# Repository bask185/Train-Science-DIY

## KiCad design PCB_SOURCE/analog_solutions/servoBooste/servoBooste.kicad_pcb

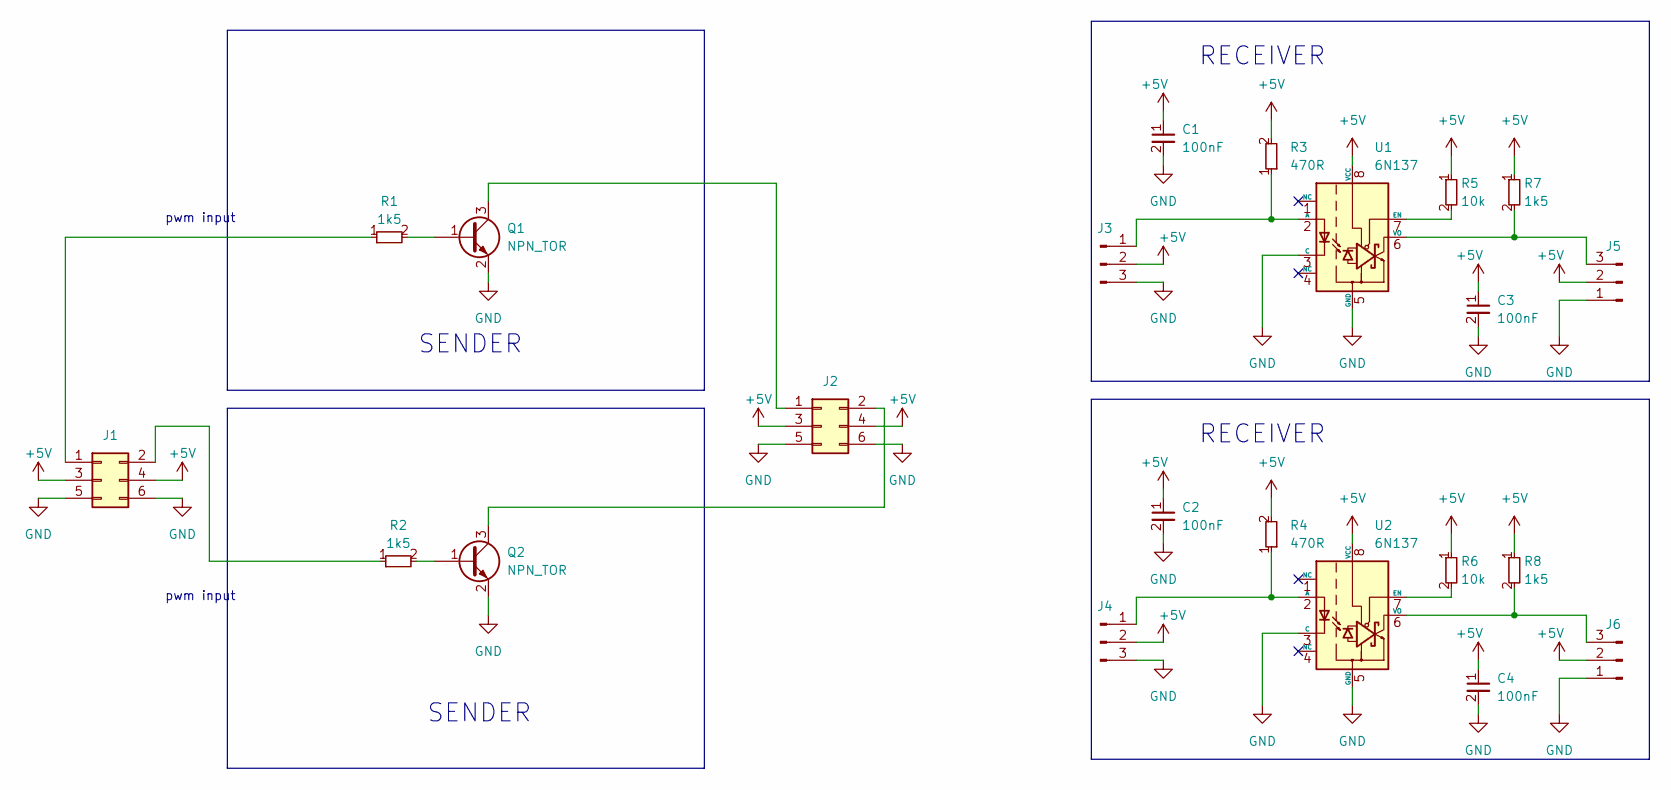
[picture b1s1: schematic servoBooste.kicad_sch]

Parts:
C1, C2, C3, C4: 100nF; C_0603_1608Metric; JLCPCB Part# C14663
J1: Conn_02x03_Odd_Even; PinSocket_2x03_P2.54mm_Vertical
J2: Conn_02x03_Odd_Even; PinHeader_2x03_P2.54mm_Vertical
J3, J4: Conn_01x03_Pin; PinSocket_1x03_P2.54mm_Horizontal
J5, J6: Conn_01x03_Pin; PinHeader_1x03_P2.54mm_Horizontal
Q1, Q2: NPN_TOR; SOT-23; JLCPCB Part# C2145
R1, R2, R7, R8: 1k5; R_0603_smalltext; JLCPCB Part# C22843
R3, R4: 470R; R_0603_smalltext; JLCPCB Part# C23179
R5, R6: 10k; R_0603_smalltext; JLCPCB Part# C25804
U1, U2: 6N137; SMDIP-8_W7.62mm

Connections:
+5V: C1.1, C2.1, C3.1, C4.1, J1.3, J1.4, J2.3, J2.4, J3.2, J4.2, J5.2, J6.2, R3.2, R4.2, R5.1, R6.1, R7.1, R8.1, U1.8 (VCC), U2.8 (VCC)
GND: C1.2, C2.2, C3.2, C4.2, J1.5, J1.6, J2.5, J2.6, J3.3, J4.3, J5.1, J6.1, Q1.2 (E), Q2.2 (E), U1.3 (C), U1.5 (GND), U2.3 (C), U2.5 (GND)
unnamed: J1.1, R1.1
unnamed: J1.2, R2.1
unnamed: J2.1, Q1.3 (C)
unnamed: J2.2, Q2.3 (C)
unnamed: J3.1, R3.1, U1.2 (A)
unnamed: J4.1, R4.1, U2.2 (A)
unnamed: J5.3, R7.2, U1.6 (VO)
unnamed: J6.3, R8.2, U2.6 (VO)
unnamed: Q1.1 (B), R1.2
unnamed: Q2.1 (B), R2.2
unnamed: R5.2, U1.7 (EN)
unnamed: R6.2, U2.7 (EN)

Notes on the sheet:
pwm input
SENDER
RECEIVER

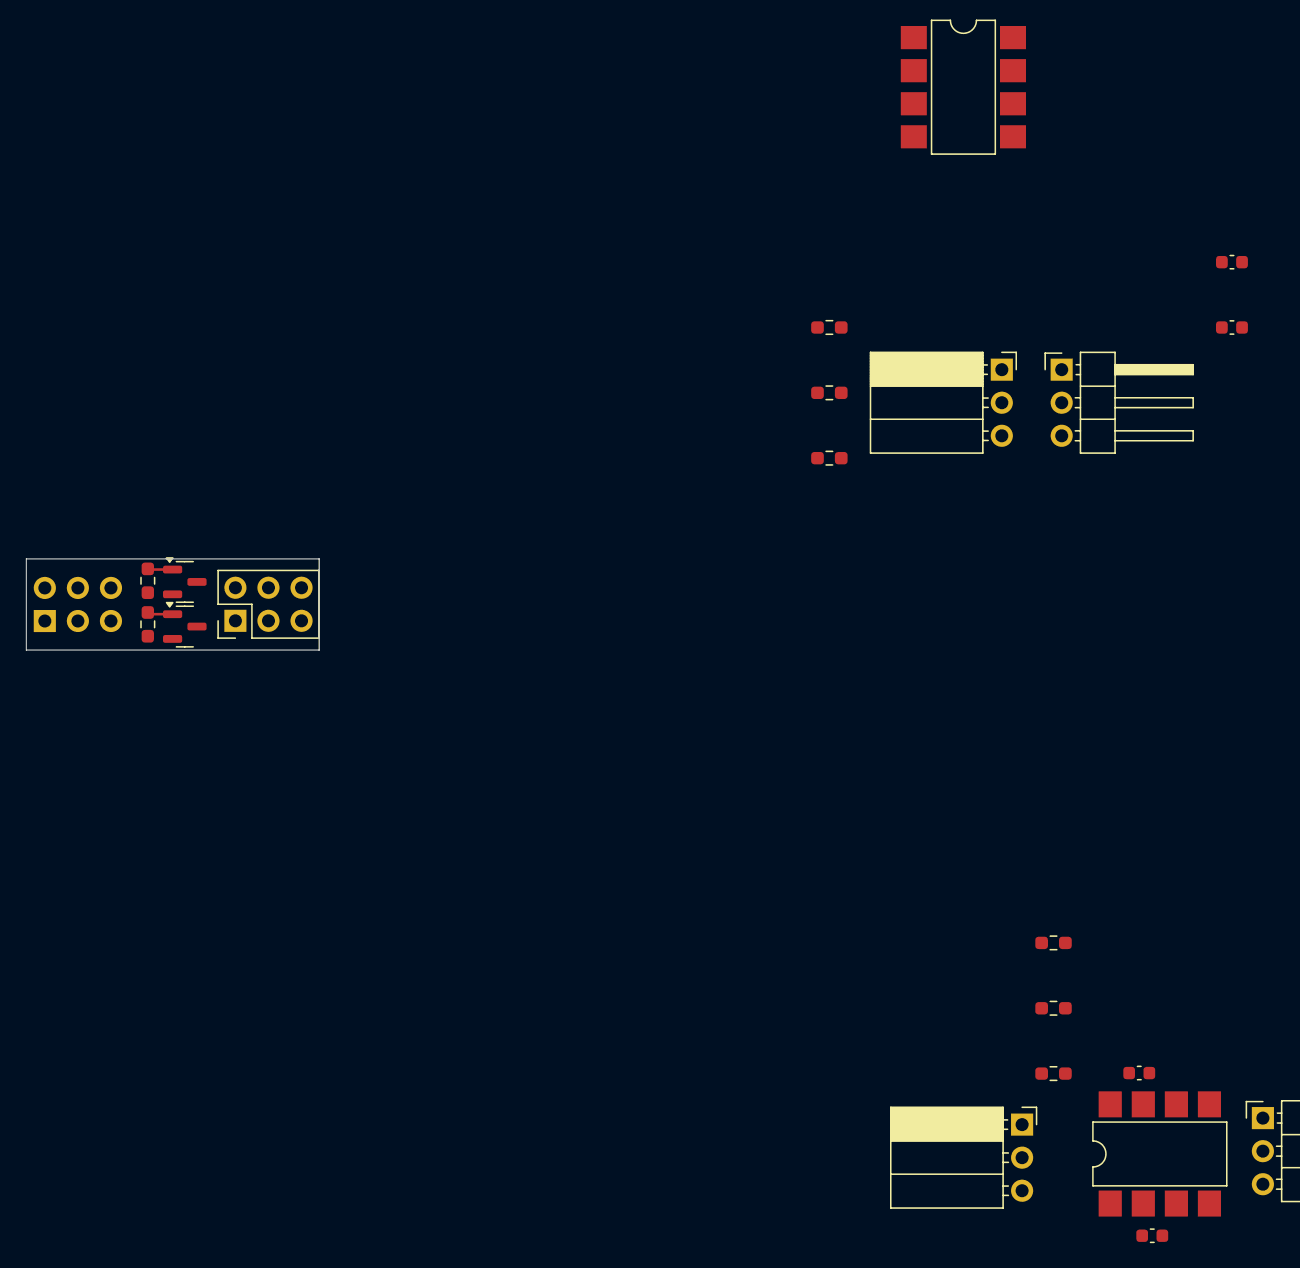
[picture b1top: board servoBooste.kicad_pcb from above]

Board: 2 copper layers, 22.5 x 7.0 mm, 22 parts (1 on the bottom side), 14 nets.

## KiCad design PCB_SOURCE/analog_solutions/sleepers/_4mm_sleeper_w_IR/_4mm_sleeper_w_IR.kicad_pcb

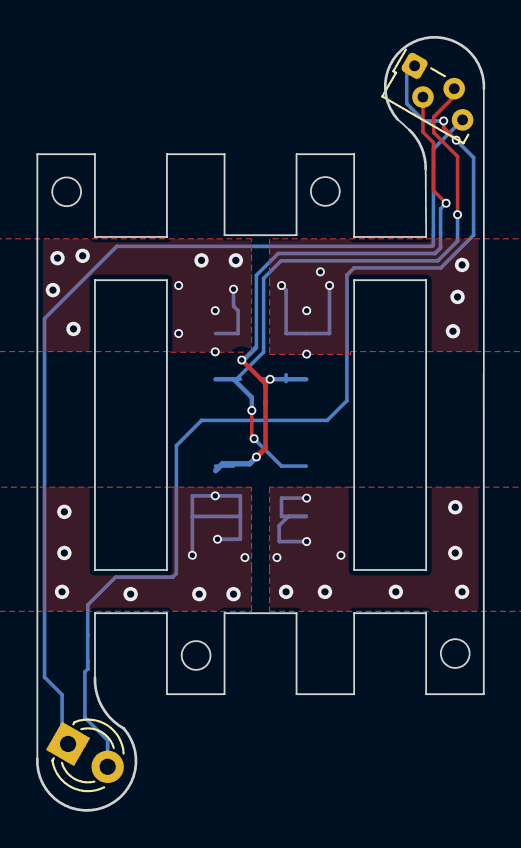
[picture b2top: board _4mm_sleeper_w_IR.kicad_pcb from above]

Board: 2 copper layers, 24.8 x 42.9 mm, 3 parts (1 on the bottom side), 4 nets.

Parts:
D101: LED; LED_D3.0mm
J106: Conn_02x05_Odd_Even; PinSocket_2x05_P2.54mm_Vertical_SMD
U101: IS471F; Sharp_IS471F

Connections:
/OUT: J106.4, J106.7, U101.2 (OUT)
GND: J106.3, J106.8, U101.3 (GND)
unnamed: D101.1 (K), U101.4 (GLo)
VCC: D101.2 (A), J106.5, J106.6, U101.1 (Vs)

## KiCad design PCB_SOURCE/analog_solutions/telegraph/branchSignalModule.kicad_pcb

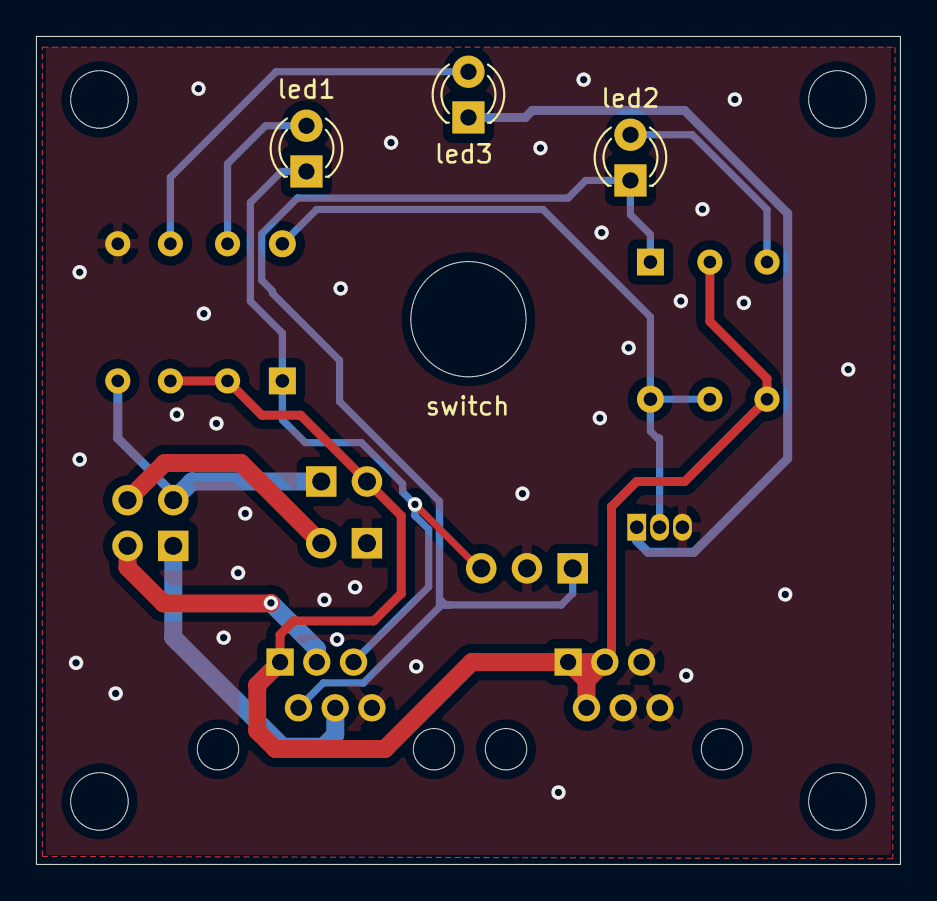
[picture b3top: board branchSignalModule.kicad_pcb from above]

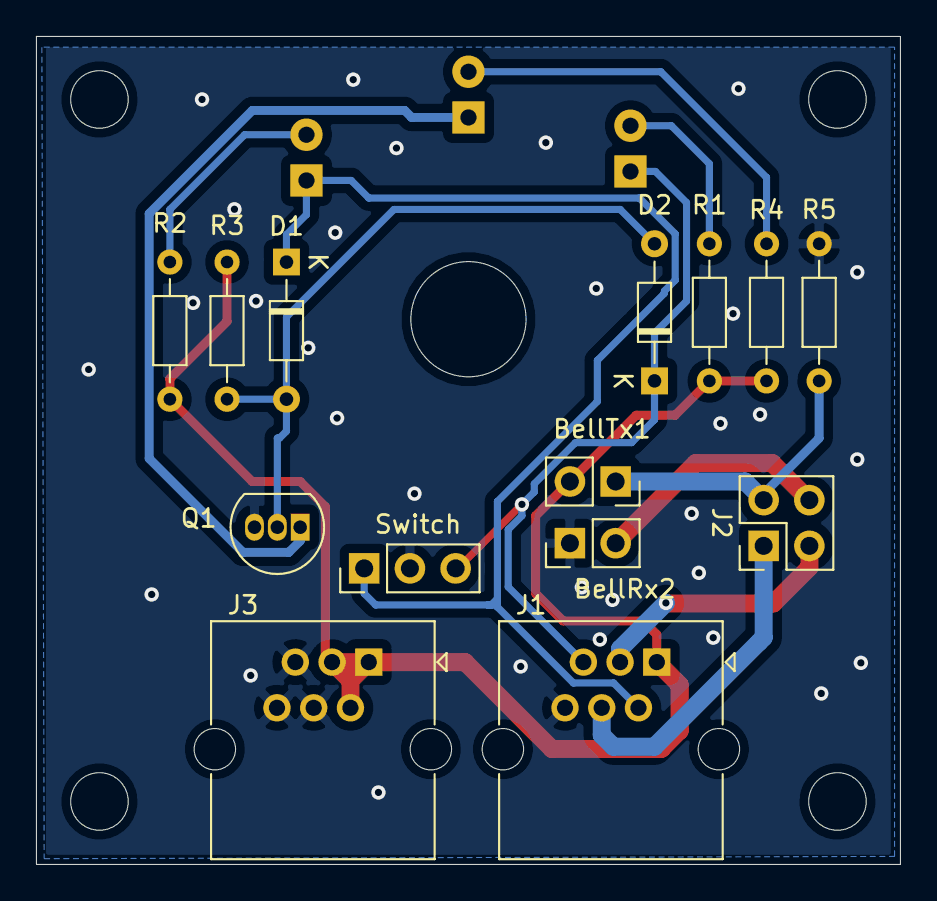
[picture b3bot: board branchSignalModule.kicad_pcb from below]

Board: 2 copper layers, 48.0 x 46.0 mm, 18 parts (14 on the bottom side), 13 nets.

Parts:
BellRx2: BellRx; PinHeader_1x02_P2.54mm_Vertical
BellTx1: bell TX; PinSocket_1x02_P2.54mm_Vertical
D1, D2: D; D_DO-34_SOD68_P7.62mm_Horizontal
J1, J3: RJ12; RJ25_Wayconn_MJEA-660X1_Horizontal
J2: JU; PinHeader_2x02_P2.54mm_Vertical
Q1: BC517; TO-92_Inline
R1, R2, R4, R5: 1k; R_Axial_DIN0204_L3.6mm_D1.6mm_P7.62mm_Horizontal
R3: 10k; R_Axial_DIN0204_L3.6mm_D1.6mm_P7.62mm_Horizontal
Switch: SW_SPDT; PinHeader_1x03_P2.54mm_Vertical
led1: train in line; LED_D3.0mm
led2: line free; LED_D3.0mm
led3: line blocked; LED_D3.0mm
switch: MountingHole_6.4mm_M6

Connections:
+12V: BellTx1.2, J1.1, J3.1, J3.2, J3.3, R1.1, R2.1, R3.1, R4.1
/bellRX: BellRx2.2, J2.4
/bellTX: BellTx1.1, J2.2, R5.1
/line1: D1.1, J1.2, Switch.1, led2.1
/line2: D2.1, J1.5, Switch.3, led1.1
GND: BellRx2.1, J1.6, J3.4, J3.5, J3.6, Q1.3, R5.2, Switch.2
unnamed: D1.2, D2.2, Q1.2, R3.2
unnamed: J1.3, J2.3
unnamed: J1.4, J2.1
unnamed: Q1.1, led3.1
unnamed: R1.2, led1.2
unnamed: R2.2, led2.2
unnamed: R4.2, led3.2

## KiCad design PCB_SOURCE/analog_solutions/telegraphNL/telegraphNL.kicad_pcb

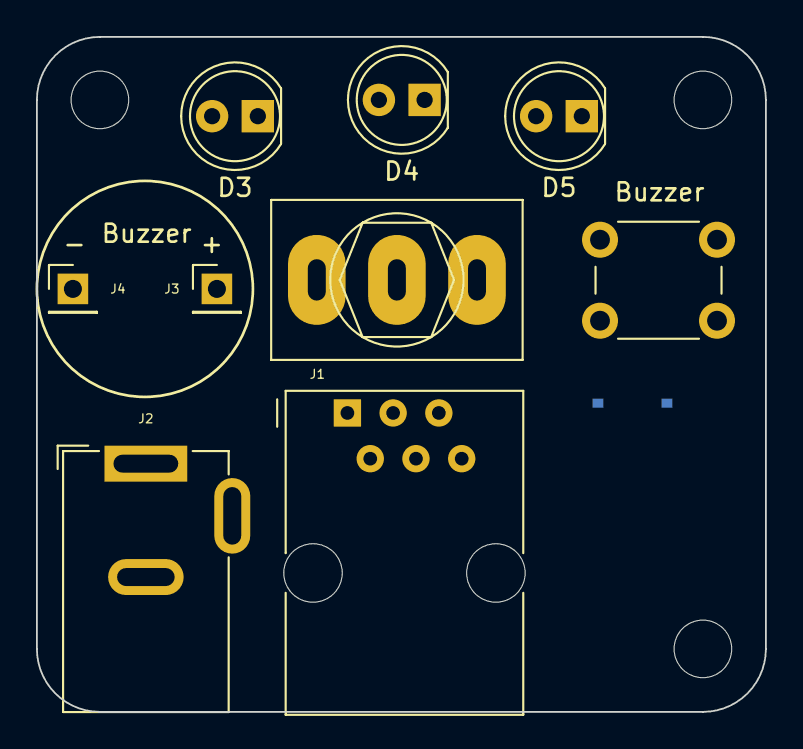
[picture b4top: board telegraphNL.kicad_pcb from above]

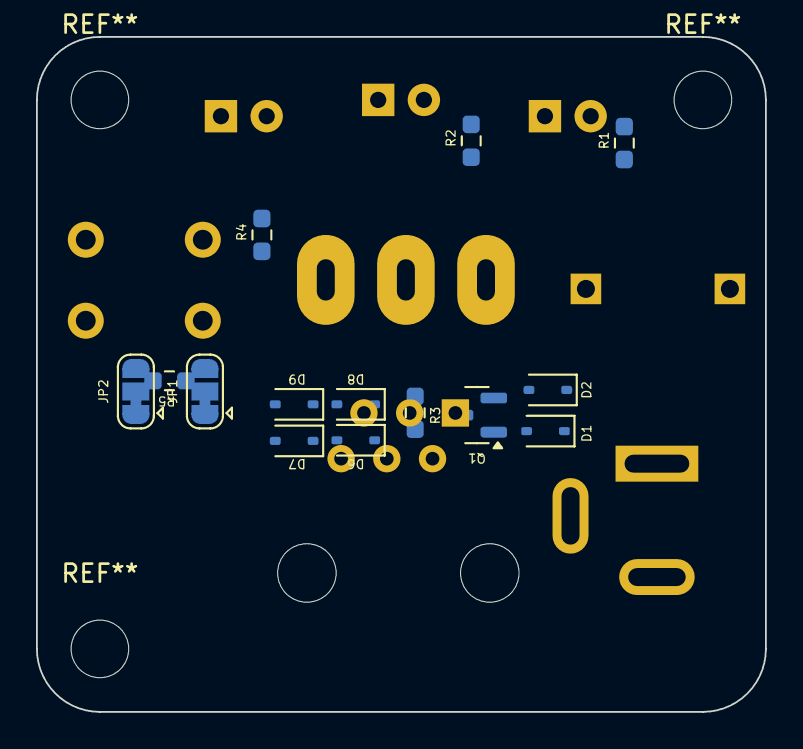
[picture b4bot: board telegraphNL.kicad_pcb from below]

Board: 2 copper layers, 40.5 x 37.5 mm, 23 parts (14 on the bottom side), 15 nets, no tracks yet.

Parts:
D1, D2, D6, D7, D8, D9: 1N4148WS; D_SOD-323
D3: YELLOW; LED_D5.0mm
D4: GREEN; LED_D5.0mm
D5: WHITE; LED_D5.0mm
J1: RJ12
J2: Barrel_Jack; barreljack
J3, J4: Conn_01x01; PinHeader_1x01_P2.54mm_Vertical
JP1, JP2: SolderJumper_3_Bridged12; SolderJumper-3_P1.3mm_Bridged12_RoundedPad1.0x1.5mm
Q1: NPN_TOR; SOT-23
R1, R2, R4: 15k; R_0603_smalltext
R3, R5: 10k; R_0603_smalltext
SW1: SW_SPDT; SW_Toggle_Blue_wSlots
SW2: 6mm_tactile; SW_PUSH_6mm_H4.3mm

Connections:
+12V: D6.1 (K), D8.1 (K), J1.1, R1.1, R2.1, R3.1, R4.1, SW2.2 (B)
/bellRX: J3.1, JP2.2 (C)
/bellTX: JP1.2 (C), R5.1, SW2.1 (A)
/line1: D1.1 (K), D4.1 (K), J1.2, SW1.1 (A)
/line2: D2.1 (K), D3.1 (K), J1.5, SW1.3 (C)
GND: D7.2 (A), D9.2 (A), J1.6, J4.1, Q1.2 (E), R5.2, SW1.2 (B)
unnamed: D1.2 (A), D2.2 (A), Q1.1 (B), R3.2
unnamed: D3.2 (A), R1.2
unnamed: D4.2 (A), R2.2
unnamed: D5.2 (A), R4.2
unnamed: D5.1 (K), Q1.3 (C)
unnamed: D6.2 (A), D7.1 (K), J2.1
unnamed: D8.2 (A), D9.1 (K), J2.2
unnamed: J1.4, JP1.1 (A), JP2.3 (B)
unnamed: J1.3, JP1.3 (B), JP2.1 (A)

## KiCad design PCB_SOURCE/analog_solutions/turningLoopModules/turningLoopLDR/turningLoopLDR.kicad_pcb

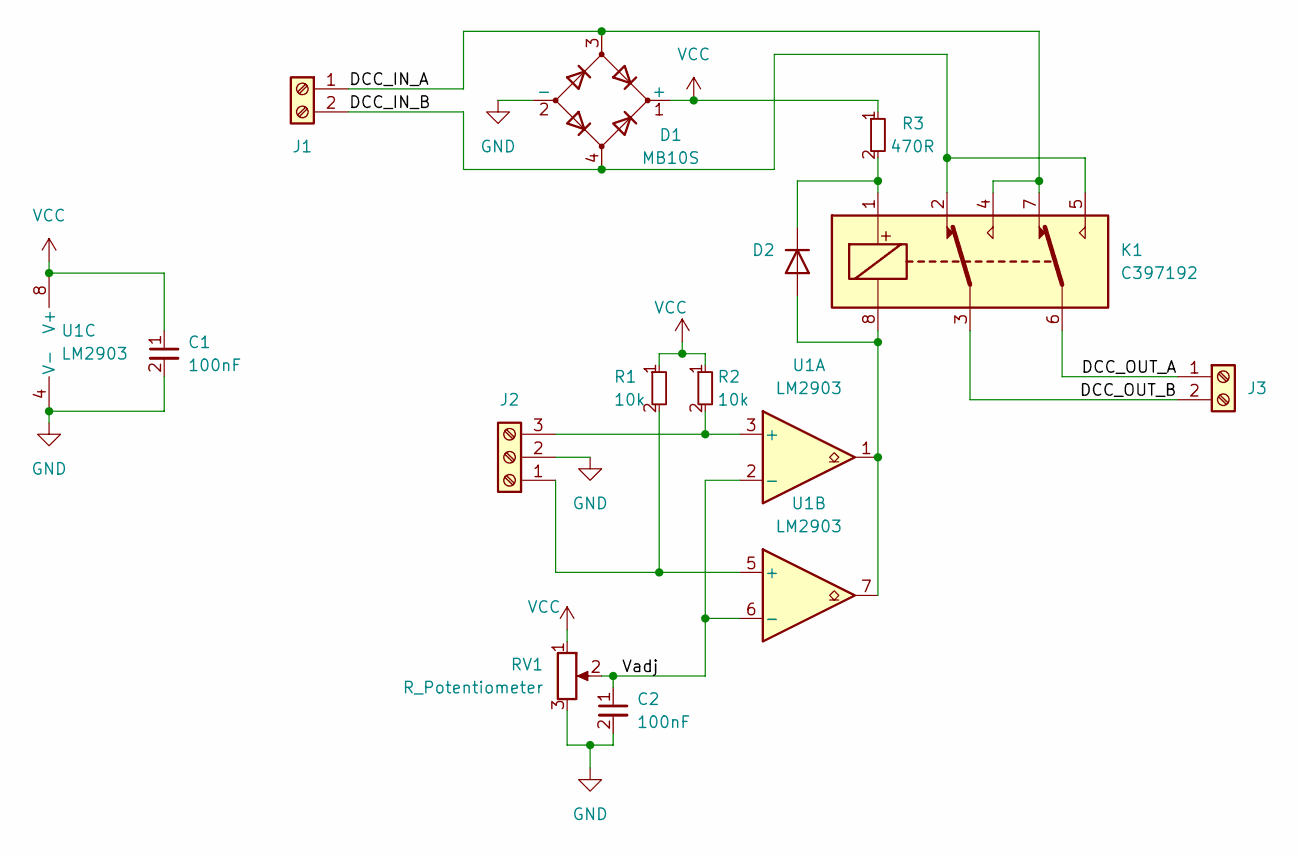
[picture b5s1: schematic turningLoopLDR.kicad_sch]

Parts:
C1, C2: 100nF; C_0603_1608Metric; JLCPCB Part# C14663
D1: MB10S; TO-269AA; JLCPCB Part# C2488
D2: 1N4148WS; D_SOD-323; JLCPCB Part# C2128
J1, J3: Screw_Terminal_01x02; TerminalBlock_Phoenix_MKDS-1,5-2-5.08_1x02_P5.08mm_Horizont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
J2: Screw_Terminal_01x03; TerminalBlock_Phoenix_MKDS-1,5-3-5.08_1x03_P5.08mm_Horizont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
K1: G6K-2F-Y-TR DC12; Relay_DPDT_Omron_G6K-2F-Y; JLCPCB Part# C397192
R1, R2: 10k; R_0603_smalltext; JLCPCB Part# C25804
R3: 470R; R_0805_handsolder-smalltext; JLCPCB Part# C17710
RV1: R_Potentiometer; Potentiometer_Bourns_TC33X_Vertical; JLCPCB Part# C128547
U1: LM2903; VSSOP-8_3.0x3.0mm_P0.65mm; JLCPCB Part# C2998739

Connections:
/DCC_IN_A: D1.3, J1.1, K1.4, K1.7
/DCC_IN_B: D1.4, J1.2, K1.2, K1.5
/DCC_OUT_A: J3.1, K1.6
/DCC_OUT_B: J3.2, K1.3
/Vadj: C2.1, RV1.2, U1.2 (-), U1.6 (-)
GND: C1.2, C2.2, D1.2 (-), J2.2, RV1.3, U1.4 (V-)
unnamed: D2.2 (A), K1.8, U1.1, U1.7
unnamed: D2.1 (K), K1.1, R3.2
unnamed: J2.1, R1.2, U1.5 (+)
unnamed: J2.3, R2.2, U1.3 (+)
VCC: C1.1, D1.1 (+), R1.1, R2.1, R3.1, RV1.1, U1.8 (V+)

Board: 2 copper layers, 13 parts (0 on the bottom side), 11 nets, no tracks yet.

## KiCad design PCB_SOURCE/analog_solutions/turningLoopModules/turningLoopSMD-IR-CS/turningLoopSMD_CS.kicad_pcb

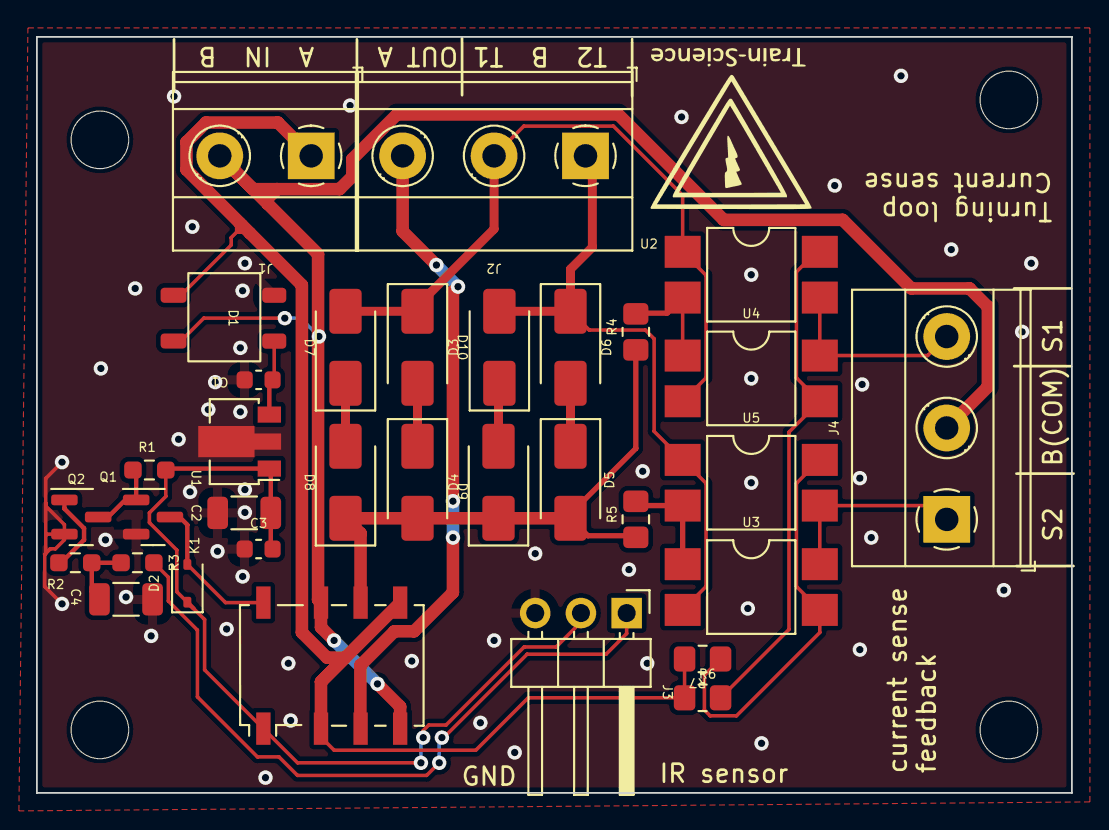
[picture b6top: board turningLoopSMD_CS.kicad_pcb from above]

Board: 2 copper layers, 57.5 x 42.0 mm, 33 parts (0 on the bottom side), 24 nets.

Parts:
C1, C3: 100nF; C_0603_1608Metric
C2, C4: 22uF; C_1206_3216Metric
D1: MB10S; MB10s
D2: 1N4148WS; D_SOD-323
D3, D4, D5, D6, D7, D8, D9, D10: D; D_SMA
J1: DCC_IN; TerminalBlock_Phoenix_MKDS-1,5-2-5.08_1x02_P5.08mm_Horizont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
J2, J4: DCC_OUT; TerminalBlock_Phoenix_MKDS-1,5-3-5.08_1x03_P5.08mm_Horizont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
J3: Conn_01x03_Male; PinHeader_1x03_P2.54mm_Horizontal
K1: G6K-2F-Y-TR DC5; Relay_DPDT_Omron_G6K-2F-Y
Q1, Q2: NPN_TOR; SOT-23
R1: 10k; R_0603_smalltext
R2, R3: 4k7; R_0603_smalltext
R4, R5: 47R; R_0805_handsolder-smalltext
R6, R7: 3k3; R_0805_handsolder-smalltext
U1: L78L12_SOT89; SOT-89-3
U2, U3, U4, U5: EL817S; SMDIP-4_W7.62mm

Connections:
+12V: C2.1, C3.2, D2.1 (K), J3.2, K1.1, R1.1, U1.1 (OUT)
/DCC_A_IN: D1.3, J1.1, K1.2, K1.5, R6.1, R7.2
/DCC_A_OUT: J2.3, K1.3
/DCC_B_IN: D1.4, J1.2, J4.2, K1.4, K1.7
/DCC_B_OUT: D4.2 (A), D5.2 (A), D8.1 (K), D9.1 (K), K1.6, R4.1, R5.1
/S1: J4.3, U2.3, U4.4
/S2: J4.1, U3.4, U5.3
/T1: D3.1 (K), D7.2 (A), J2.2, U2.1, U4.2
/T2: D6.1 (K), D10.2 (A), J2.1, U3.2, U5.1
GND: C1.1, C2.2, C3.1, C4.2, D1.2 (-), J3.3, Q1.2 (E), Q2.2 (E), U1.2 (GND)
unnamed: C4.1, R2.2, R3.1
unnamed: D2.2 (A), K1.8, Q1.3 (C)
unnamed: D3.2 (A), D4.1 (K)
unnamed: D5.1 (K), D6.2 (A)
unnamed: D7.1 (K), D8.2 (A)
unnamed: D9.2 (A), D10.1 (K)
unnamed: J3.1, R3.2
unnamed: Q1.1 (B), Q2.3 (C), R1.2
unnamed: Q2.1 (B), R2.1
unnamed: R4.2, U2.2, U4.1
unnamed: R5.2, U3.1, U5.2
unnamed: R6.2, U2.4, U4.3
unnamed: R7.1, U3.3, U5.4
VCC: C1.2, D1.1 (+), U1.3 (IN)
